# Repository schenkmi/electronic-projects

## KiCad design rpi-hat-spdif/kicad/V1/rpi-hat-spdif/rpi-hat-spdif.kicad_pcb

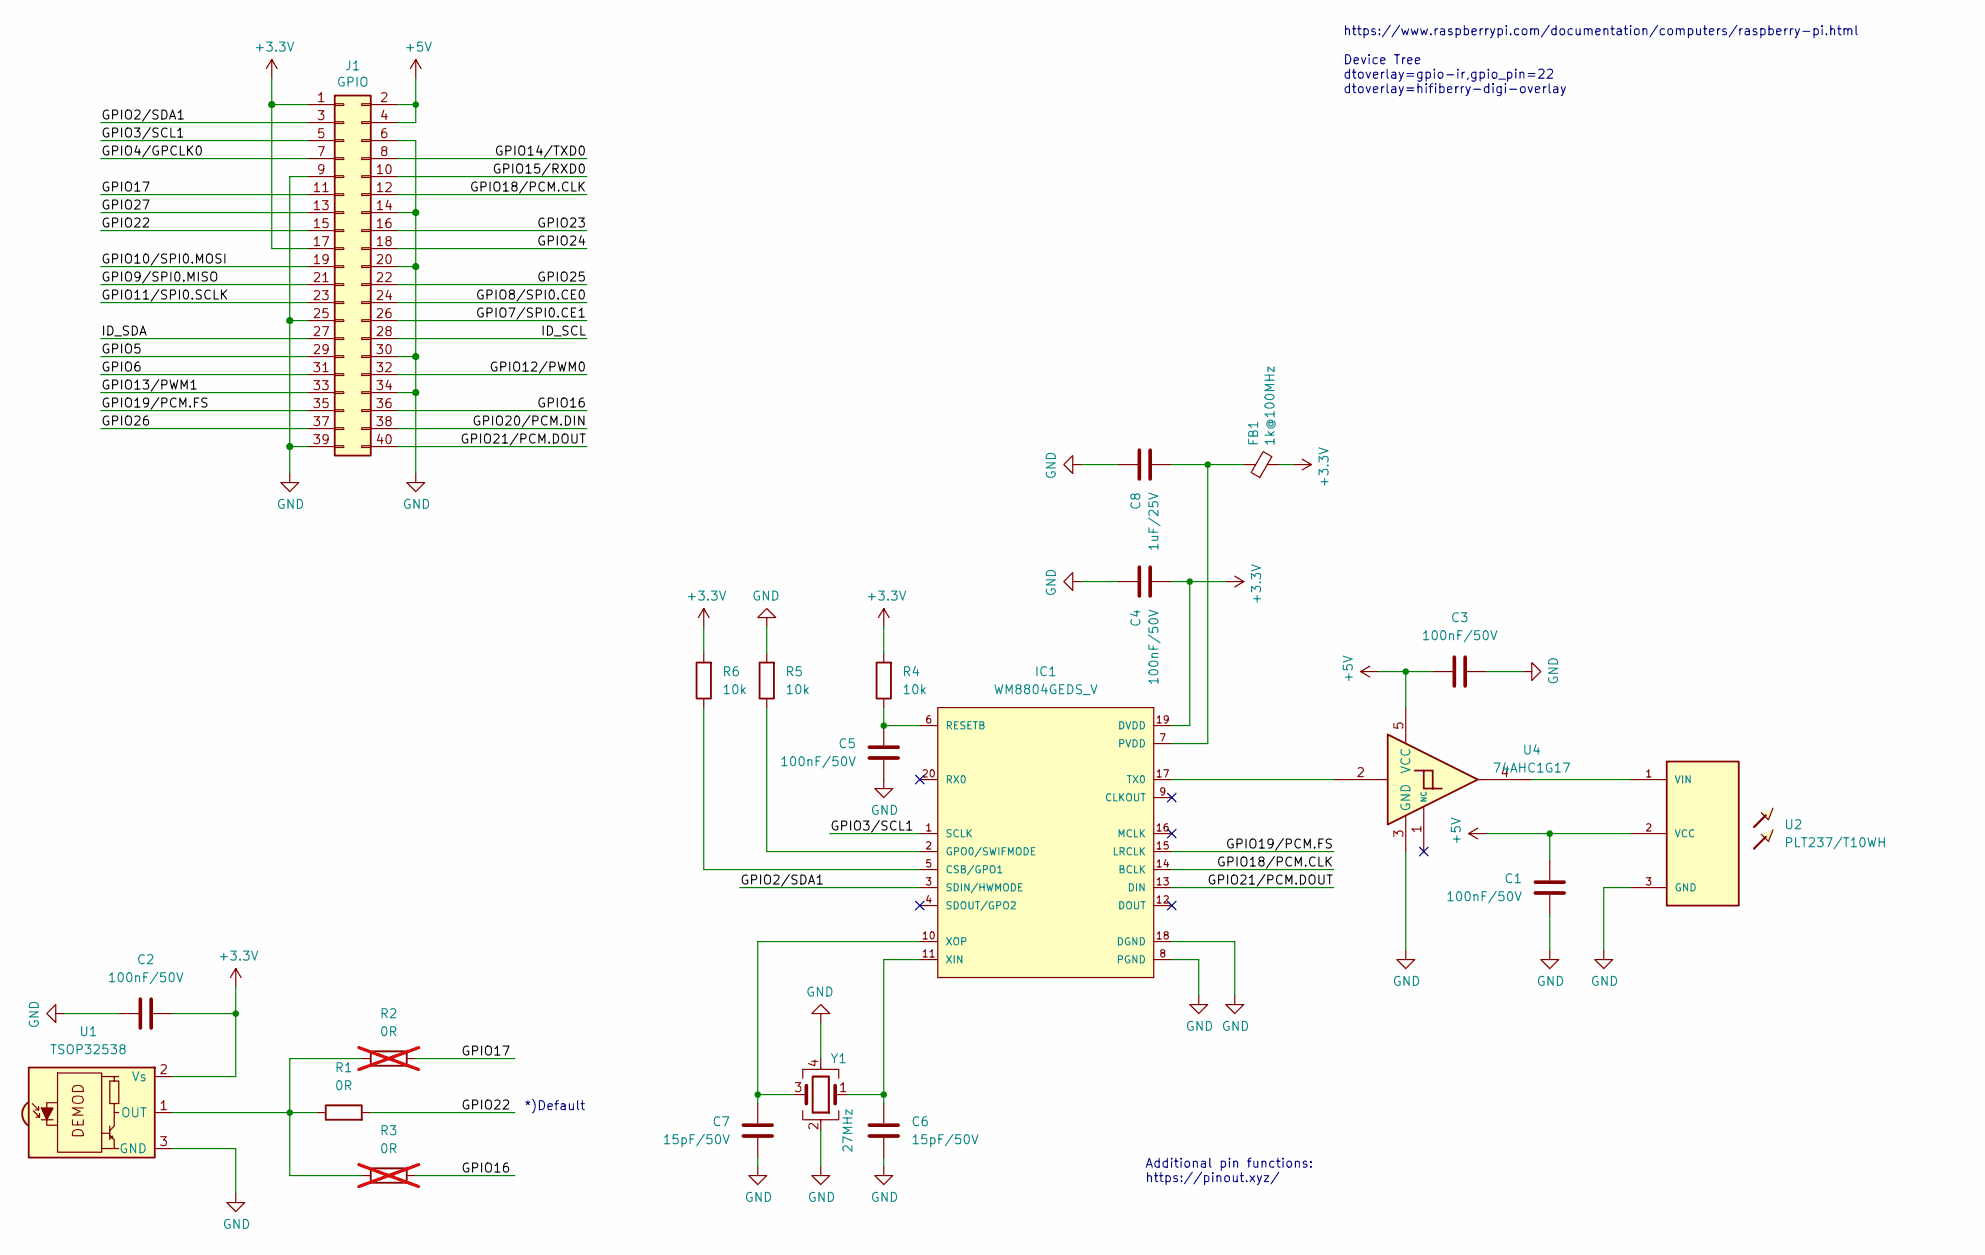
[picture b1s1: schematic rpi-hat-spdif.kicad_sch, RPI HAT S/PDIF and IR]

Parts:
C1, C2, C3, C4, C5: 100nF/50V; C_0603_1608Metric
C6, C7: 15pF/50V; C_0603_1608Metric
C8: 1uF/25V; C_0603_1608Metric
FB1: 1k@100MHz; R_0603_1608Metric
IC1: WM8804GEDS_V; SSOP-20_5.3x7.2mm_P0.65mm
J1: GPIO; PinSocket_2x20_P2.54mm_Vertical
R1: 0R; R_0603_1608Metric
R2, R3: 0R; R_0603_1608Metric; not fitted
R4, R5, R6: 10k; R_0603_1608Metric
U1: TSOP32538; Vishay_MOLD-3Pin
U2: PLT237/T10WH; PLR135-T10_PLT133-T10W
U4: 74AHC1G17; SOT-23-5
Y1: 27MHz; Crystal_SMD_3225-4Pin_3.2x2.5mm_HandSoldering

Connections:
+3V3: C2.2, C4.2, FB1.2, IC1.19 (DVDD), J1.1, J1.17, R4.2, R6.2, U1.2 (Vs)
+5V: C1.1, C3.1, J1.2, J1.4, U2.2 (VCC), U4.5 (VCC)
/GPIO2/SDA1: IC1.3 (SDIN/HWMODE), J1.3
/GPIO3/SCL1: IC1.1 (SCLK), J1.5
/GPIO4/GPCLK0: J1.7
/GPIO5: J1.29
/GPIO6: J1.31
/GPIO7/SPI0.CE1: J1.26
/GPIO8/SPI0.CE0: J1.24
/GPIO9/SPI0.MISO: J1.21
/GPIO10/SPI0.MOSI: J1.19
/GPIO11/SPI0.SCLK: J1.23
/GPIO12/PWM0: J1.32
/GPIO13/PWM1: J1.33
/GPIO14/TXD0: J1.8
/GPIO15/RXD0: J1.10
/GPIO16: J1.36, R3.2
/GPIO17: J1.11, R2.2
/GPIO18/PCM.CLK: IC1.14 (BCLK), J1.12
/GPIO19/PCM.FS: IC1.15 (LRCLK), J1.35
/GPIO20/PCM.DIN: J1.38
/GPIO21/PCM.DOUT: IC1.13 (DIN), J1.40
/GPIO22: J1.15, R1.2
/GPIO23: J1.16
/GPIO24: J1.18
/GPIO25: J1.22
/GPIO26: J1.37
/GPIO27: J1.13
/ID_SCL: J1.28
/ID_SDA: J1.27
GND: C1.2, C2.1, C3.2, C4.1, C5.2, C6.1, C7.2, C8.1, IC1.8 (PGND), IC1.18 (DGND), J1.6, J1.9, J1.14, J1.20, J1.25, J1.30, J1.34, J1.39, R5.2, U1.3 (GND), U2.3 (GND), U4.3 (GND), Y1.2, Y1.4
unnamed: IC1.5 (CSB/GPO1), R6.1
unnamed: IC1.2 (GPO0/SWIFMODE), R5.1
unnamed: C8.2, FB1.1, IC1.7 (PVDD)
unnamed: C5.1, IC1.6 (RESETB), R4.1
unnamed: IC1.17 (TX0), U4.2
unnamed: C6.2, IC1.11 (XIN), Y1.1
unnamed: C7.1, IC1.10 (XOP), Y1.3
unnamed: R1.1, R2.1, R3.1, U1.1 (OUT)
unnamed: U2.1 (VIN), U4.4

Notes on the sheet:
https://www.raspberrypi.com/documentation/computers/raspberry-pi.html Device Tree dtoverlay=gpio-ir,gpio_pin=22 dtoverlay=hifiberry-digi-overlay
*)Default
Additional pin functions: https://pinout.xyz/

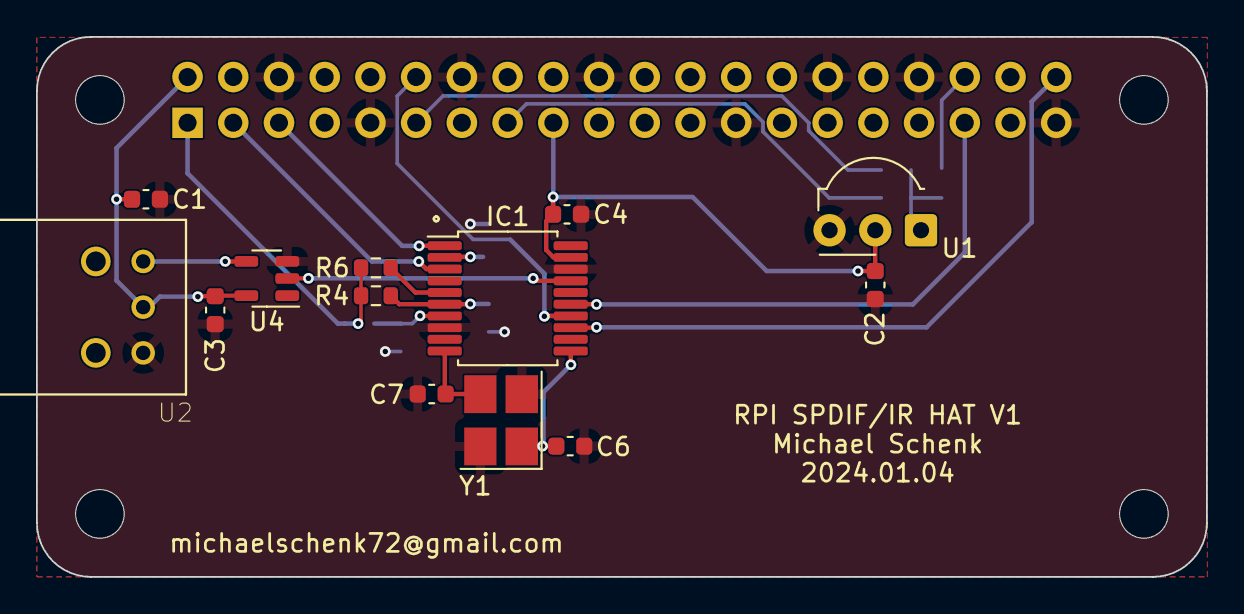
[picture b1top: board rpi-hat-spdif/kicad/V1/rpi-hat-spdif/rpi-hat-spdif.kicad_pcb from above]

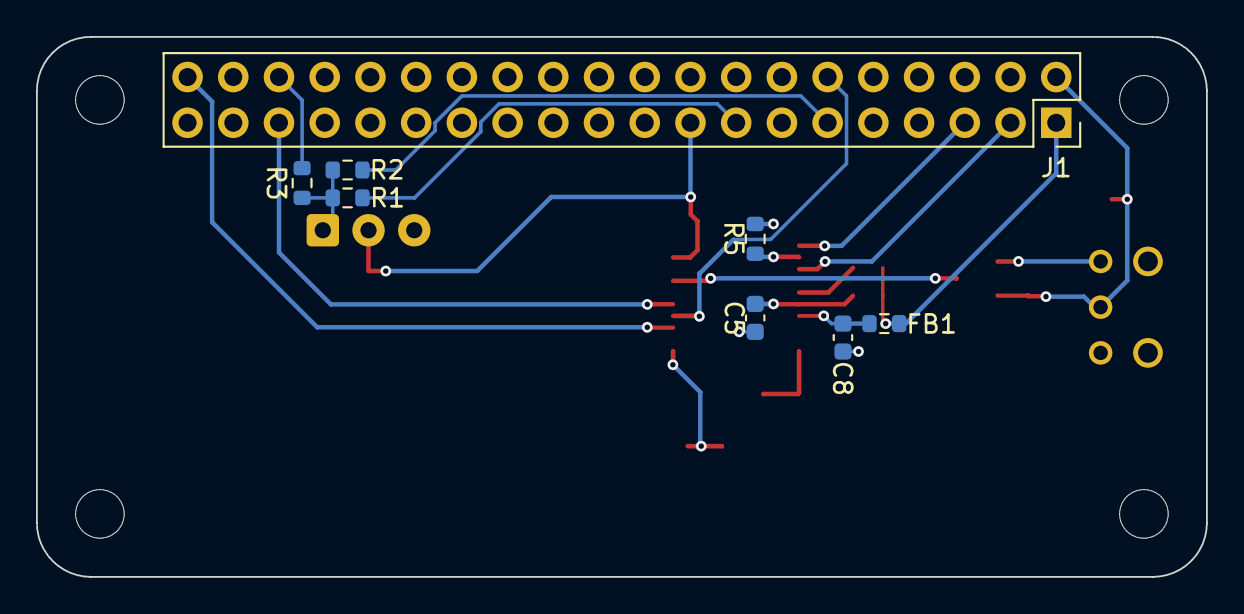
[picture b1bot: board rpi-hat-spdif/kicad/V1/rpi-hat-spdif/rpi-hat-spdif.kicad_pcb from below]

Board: 2 copper layers, 65.0 x 30.0 mm, 25 parts (8 on the bottom side), 20 nets.

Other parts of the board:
MH1, MH2, MH3, MH4: MountingHole_2.7mm_M2.5

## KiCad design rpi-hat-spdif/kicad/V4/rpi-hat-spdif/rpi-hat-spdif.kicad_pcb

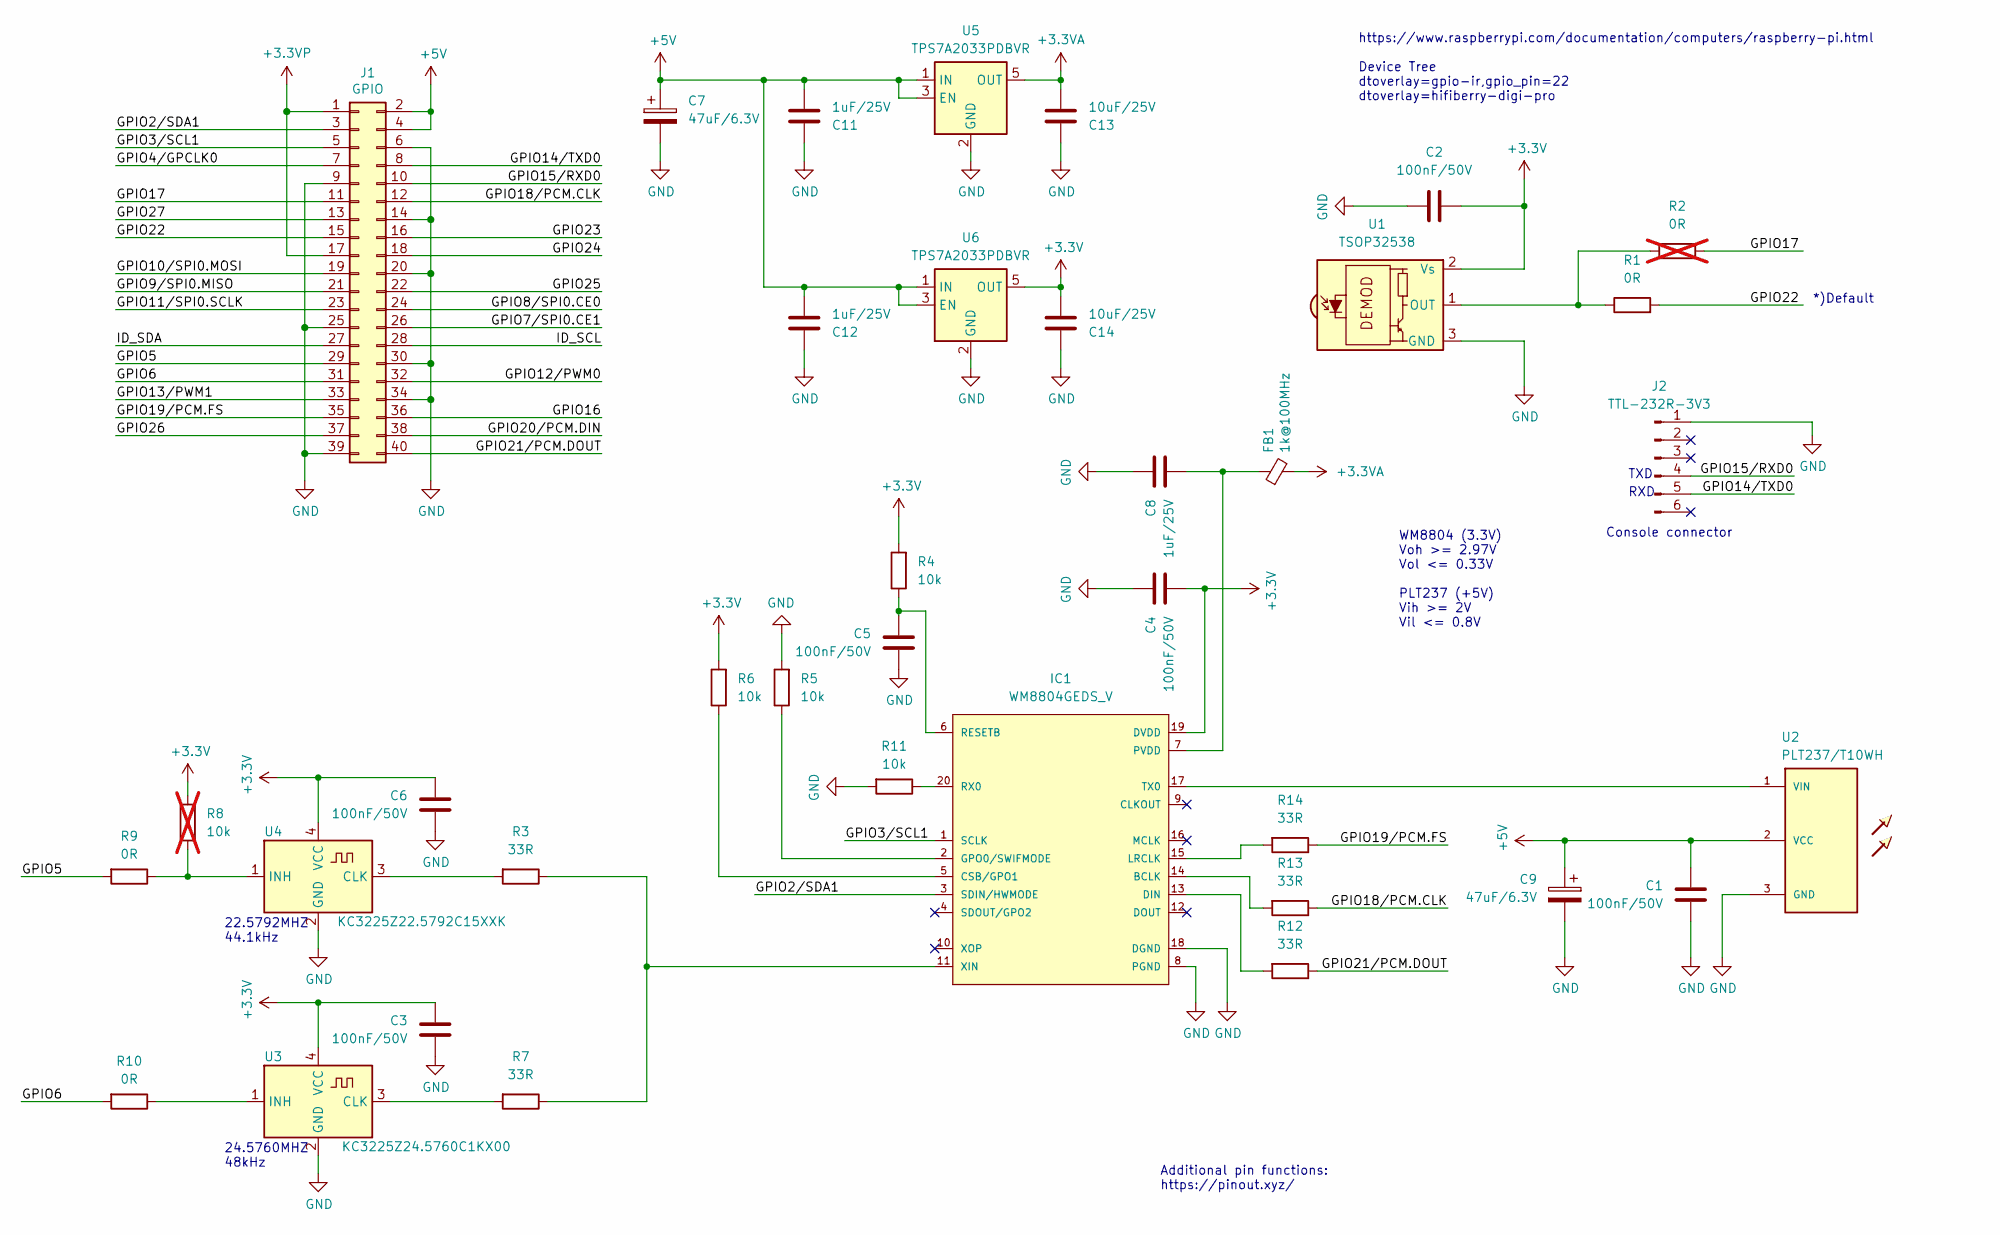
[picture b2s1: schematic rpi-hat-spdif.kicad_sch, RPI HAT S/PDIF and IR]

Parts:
C1, C2, C4: 100nF/50V; C_0603_1608Metric_Pad1.08x0.95mm_HandSolder
C3, C5, C6: 100nF/50V; C_0603_1608Metric
C7, C9: 47uF/6.3V; C_1206_3216Metric_Pad1.33x1.80mm_HandSolder
C8, C11, C12: 1uF/25V; C_0603_1608Metric_Pad1.08x0.95mm_HandSolder
C13, C14: 10uF/25V; C_1206_3216Metric_Pad1.33x1.80mm_HandSolder
FB1: 1k@100MHz; R_0603_1608Metric_Pad0.98x0.95mm_HandSolder
IC1: WM8804GEDS_V; SSOP-20_5.3x7.2mm_P0.65mm
J1: GPIO; PinSocket_2x20_P2.54mm_Vertical
J2: TTL-232R-3V3; PinHeader_1x06_P2.54mm_Vertical
R1, R9, R10: 0R; R_0603_1608Metric_Pad0.98x0.95mm_HandSolder
R2: 0R; R_0603_1608Metric_Pad0.98x0.95mm_HandSolder; not fitted
R3, R7, R12, R13, R14: 33R; R_0603_1608Metric_Pad0.98x0.95mm_HandSolder
R4, R5, R6, R11: 10k; R_0603_1608Metric_Pad0.98x0.95mm_HandSolder
R8: 10k; R_0603_1608Metric_Pad0.98x0.95mm_HandSolder; not fitted
U1: TSOP32538; Vishay_MOLD-3Pin
U2: PLT237/T10WH; PLR135-T10_PLT133-T10W
U3: KC3225Z24.5760C1KX00; Crystal_SMD_3225-4Pin_3.2x2.5mm_HandSoldering
U4: KC3225Z22.5792C15XXK; Crystal_SMD_3225-4Pin_3.2x2.5mm_HandSoldering
U5, U6: TPS7A2033PDBVR; SOT-23-5

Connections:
+3.3VA: C13.2, FB1.2, U5.5 (OUT)
+3.3VP: J1.1, J1.17
+3V3: C2.2, C3.1, C4.2, C6.1, C14.2, IC1.19 (DVDD), R4.2, R6.2, R8.2, U1.2 (Vs), U3.4 (VCC), U4.4 (VCC), U6.5 (OUT)
+5V: C1.1, C7.1, C9.1, C11.2, C12.2, J1.2, J1.4, U2.2 (VCC), U5.1 (IN), U5.3 (EN), U6.1 (IN), U6.3 (EN)
/GPIO2/SDA1: IC1.3 (SDIN/HWMODE), J1.3
/GPIO3/SCL1: IC1.1 (SCLK), J1.5
/GPIO4/GPCLK0: J1.7
/GPIO5: J1.29, R9.2
/GPIO6: J1.31, R10.2
/GPIO7/SPI0.CE1: J1.26
/GPIO8/SPI0.CE0: J1.24
/GPIO9/SPI0.MISO: J1.21
/GPIO10/SPI0.MOSI: J1.19
/GPIO11/SPI0.SCLK: J1.23
/GPIO12/PWM0: J1.32
/GPIO13/PWM1: J1.33
/GPIO14/TXD0: J1.8, J2.5
/GPIO15/RXD0: J1.10, J2.4
/GPIO16: J1.36
/GPIO17: J1.11, R2.2
/GPIO18/PCM.CLK: J1.12, R13.1
/GPIO19/PCM.FS: J1.35, R14.1
/GPIO20/PCM.DIN: J1.38
/GPIO21/PCM.DOUT: J1.40, R12.1
/GPIO22: J1.15, R1.2
/GPIO23: J1.16
/GPIO24: J1.18
/GPIO25: J1.22
/GPIO26: J1.37
/GPIO27: J1.13
/ID_SCL: J1.28
/ID_SDA: J1.27
GND: C1.2, C2.1, C3.2, C4.1, C5.2, C6.2, C7.2, C8.1, C9.2, C11.1, C12.1, C13.1, C14.1, IC1.8 (PGND), IC1.18 (DGND), J1.6, J1.9, J1.14, J1.20, J1.25, J1.30, J1.34, J1.39, J2.1, R5.2, R11.2, U1.3 (GND), U2.3 (GND), U3.2 (GND), U4.2 (GND), U5.2 (GND), U6.2 (GND)
unnamed: IC1.14 (BCLK), R13.2
unnamed: IC1.5 (CSB/GPO1), R6.1
unnamed: IC1.13 (DIN), R12.2
unnamed: IC1.2 (GPO0/SWIFMODE), R5.1
unnamed: IC1.15 (LRCLK), R14.2
unnamed: C8.2, FB1.1, IC1.7 (PVDD)
unnamed: C5.1, IC1.6 (RESETB), R4.1
unnamed: IC1.20 (RX0), R11.1
unnamed: IC1.17 (TX0), U2.1 (VIN)
unnamed: IC1.11 (XIN), R3.1, R7.1
unnamed: R1.1, R2.1, U1.1 (OUT)
unnamed: R7.2, U3.3 (CLK)
unnamed: R10.1, U3.1 (INH)
unnamed: R3.2, U4.3 (CLK)
unnamed: R8.1, R9.1, U4.1 (INH)

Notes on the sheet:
24.5760MHZ 48kHz
TXD
Console connector
https://www.raspberrypi.com/documentation/computers/raspberry-pi.html Device Tree dtoverlay=gpio-ir,gpio_pin=22 dtoverlay=hifiberry-digi-pro
WM8804 (3.3V) Voh >= 2.97V Vol <= 0.33V PLT237 (+5V) Vih >= 2V Vil <= 0.8V
22.5792MHZ 44.1kHz
RXD
*)Default
Additional pin functions: https://pinout.xyz/

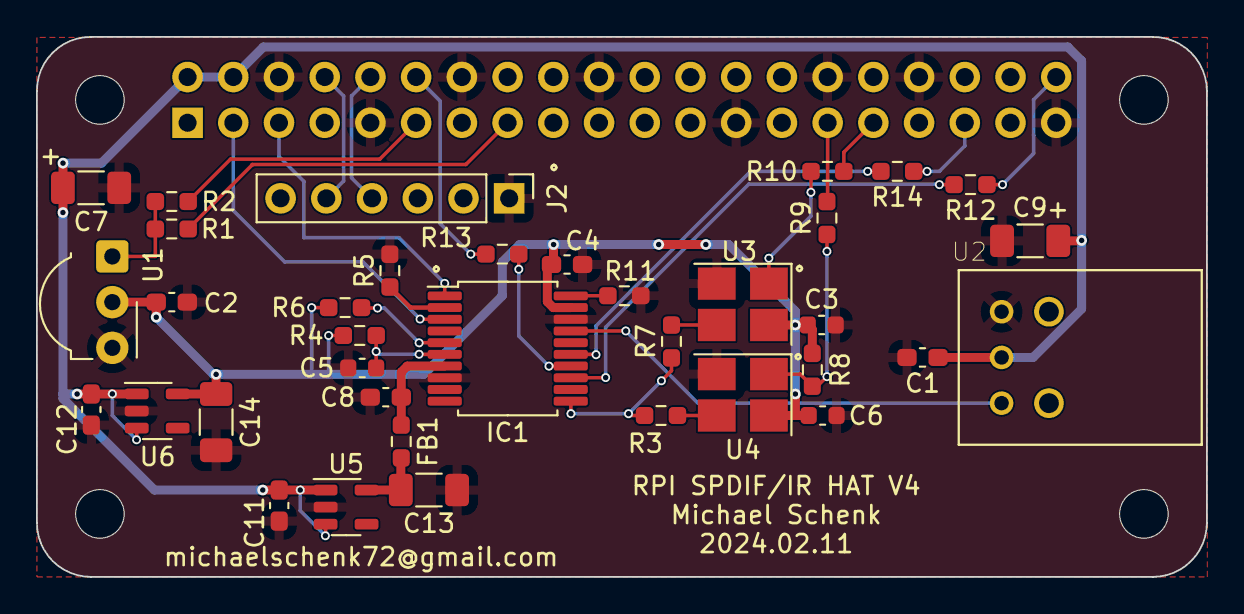
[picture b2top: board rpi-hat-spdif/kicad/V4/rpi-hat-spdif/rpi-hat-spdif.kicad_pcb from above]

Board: 2 copper layers, 65.0 x 30.0 mm, 41 parts (1 on the bottom side), 31 nets.

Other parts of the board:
MH1, MH2, MH3, MH4: MountingHole_2.7mm_M2.5
